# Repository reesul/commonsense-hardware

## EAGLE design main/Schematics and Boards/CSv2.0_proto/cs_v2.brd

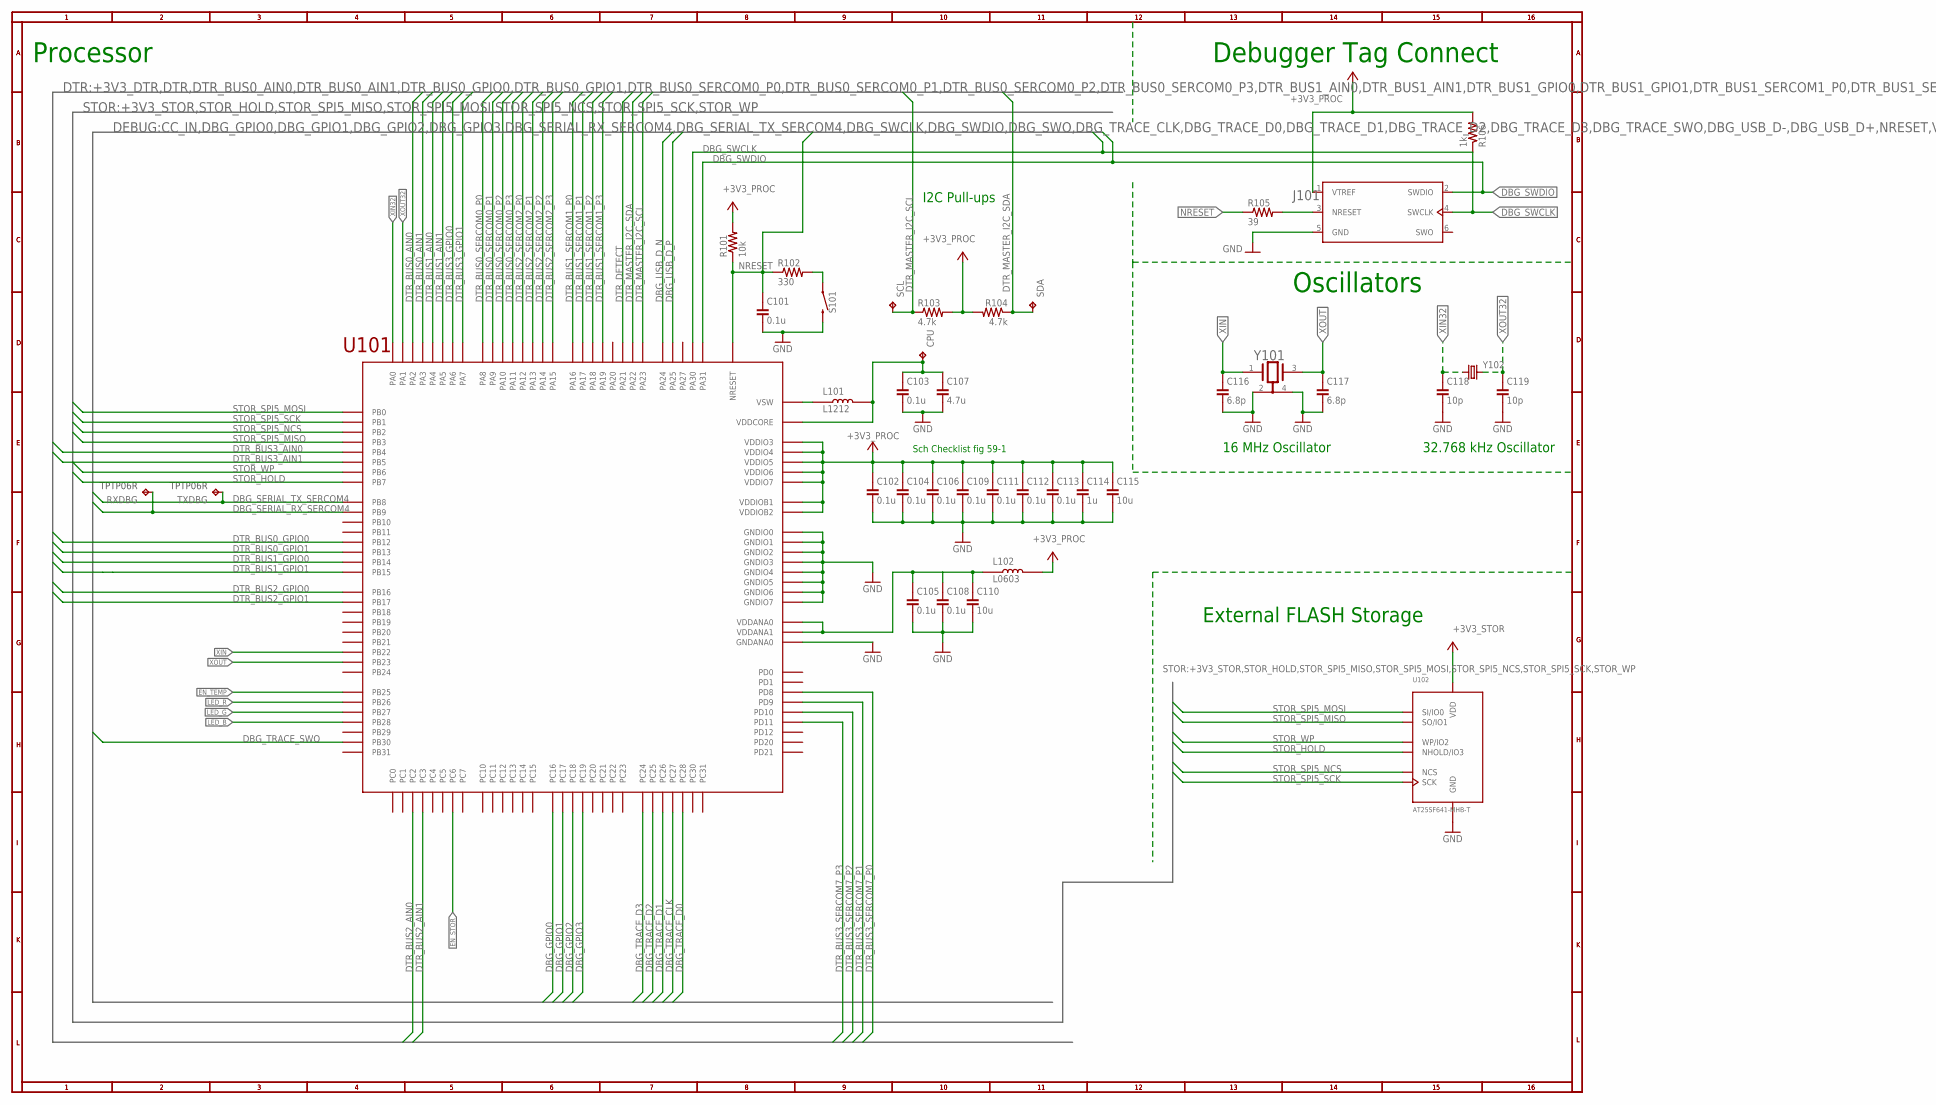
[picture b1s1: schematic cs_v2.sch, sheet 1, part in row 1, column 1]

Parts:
C101, C102, C103, C104, C105, C106, C108, C109, C111, C112, C113: 0.1u; C0402; VOLTAGE 10V; PART_NO C0402C104K8RACTU
C107: 4.7u; C0805; VOLTAGE 10V; PART_NO C0805C475K8RACTU
C110, C115: 10u; C0805; VOLTAGE 10V; PART_NO C0805C106M8RACTU
C114: 1u; C0402; VOLTAGE 10V; PART_NO C0402C105M8PACTU
C116, C117: 6.8p; C0402; PART_NO C0402C689D8GAC7867
C118, C119: 10p; C0402; PART_NO C0402C100C8GACTU
CPU: TPTP06R; TP06R
J101: J-JTAG-CORTEX-NEEDLE6-LEGS; 8.06.16_6-PIN_NEEDLE_ADAPTER_LEGS
L101: L1212; PART_NO LQH3NPN100MMEL
L102: L0603; PART_NO BLM18PG471SN1D
R101: 10k; R0402; PART_NO ERJ-2GEJ103X
R102: 330; R0402; PART_NO ERJ-2GEJ331X
R103, R104: 4.7k; R0402; PART_NO ERJ-2GEJ472X
R105: 39; R0402; PART_NO ERJ-2GEJ390X
R106: 1k; R0402; PART_NO ERJ-2GEJ102X
RXDBG: TPTP06R; TP06R
S101: SW_EVQ-P7L01P_SPST_RA; SW_EVQ-P7L01P
SCL: TPTP06R; TP06R
SDA: TPTP06R; TP06R
TXDBG: TPTP06R; TP06R
U101: ATSAMD51; TFBGA120
U102: AT25SF641-MHB-T; 8-UDFN
Y101: 16M; XTAL_EPSON_TSX3225; PART_NO TSX-3225 16.0000MF09Z-AC3
Y102: ABS07-32.768KHZ-9-T; XTAL320X150X90

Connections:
+3V3_PROC: C102.1, C104.1, C106.1, C109.1, C111.1, C112.1, C113.1, C114.1, C115.1, J101.1 (VTREF), L102.2, R101.2, R103.2, R104.2, R106.2, U101.VDDIO3, U101.VDDIO4, U101.VDDIO5, U101.VDDIO6, U101.VDDIO7, U101.VDDIOB1, U101.VDDIOB2; also elsewhere on the board
+3V3_STOR: U102.8 (VDD); also elsewhere on the board
DBG_GPIO0: U101.PC16; also elsewhere on the board
DBG_GPIO1: U101.PC17; also elsewhere on the board
DBG_GPIO2: U101.PC18; also elsewhere on the board
DBG_GPIO3: U101.PC19; also elsewhere on the board
DBG_SERIAL_RX_SERCOM4: RXDBG.TP, U101.PB09 (PB9); also elsewhere on the board
DBG_SERIAL_TX_SERCOM4: TXDBG.TP, U101.PB08 (PB8); also elsewhere on the board
DBG_SWCLK: J101.4 (SWCLK), R106.1, U101.PA30; also elsewhere on the board
DBG_SWDIO: J101.2 (SWDIO), U101.PA31; also elsewhere on the board
DBG_TRACE_CLK: U101.PC27; also elsewhere on the board
DBG_TRACE_D0: U101.PC28; also elsewhere on the board
DBG_TRACE_D1: U101.PC26; also elsewhere on the board
DBG_TRACE_D2: U101.PC25; also elsewhere on the board
DBG_TRACE_D3: U101.PC24; also elsewhere on the board
DBG_TRACE_SWO: U101.PB30; also elsewhere on the board
DBG_USB_D_N: U101.PA24; also elsewhere on the board
DBG_USB_D_P: U101.PA25; also elsewhere on the board
DTR_BUS0_AIN0: U101.PA02 (PA2); also elsewhere on the board
DTR_BUS0_AIN1: U101.PA03 (PA3); also elsewhere on the board
DTR_BUS0_GPIO0: U101.PB12; also elsewhere on the board
DTR_BUS0_GPIO1: U101.PB13; also elsewhere on the board
DTR_BUS0_SERCOM0_P0: U101.PA08 (PA8); also elsewhere on the board
DTR_BUS0_SERCOM0_P1: U101.PA09 (PA9); also elsewhere on the board
DTR_BUS0_SERCOM0_P2: U101.PA10; also elsewhere on the board
DTR_BUS0_SERCOM0_P3: U101.PA11; also elsewhere on the board
DTR_BUS1_AIN0: U101.PA04 (PA4); also elsewhere on the board
DTR_BUS1_AIN1: U101.PA05 (PA5); also elsewhere on the board
DTR_BUS1_GPIO0: U101.PB14; also elsewhere on the board
DTR_BUS1_GPIO1: U101.PB15; also elsewhere on the board
DTR_BUS1_SERCOM1_P0: U101.PA16; also elsewhere on the board
DTR_BUS1_SERCOM1_P1: U101.PA17; also elsewhere on the board
DTR_BUS1_SERCOM1_P2: U101.PA18; also elsewhere on the board
DTR_BUS1_SERCOM1_P3: U101.PA19; also elsewhere on the board
DTR_BUS2_AIN0: U101.PC02 (PC2); also elsewhere on the board
DTR_BUS2_AIN1: U101.PC03 (PC3); also elsewhere on the board
DTR_BUS2_GPIO0: U101.PB16; also elsewhere on the board
DTR_BUS2_GPIO1: U101.PB17; also elsewhere on the board
DTR_BUS2_SERCOM2_P0: U101.PA12; also elsewhere on the board
DTR_BUS2_SERCOM2_P1: U101.PA13; also elsewhere on the board
DTR_BUS2_SERCOM2_P2: U101.PA14; also elsewhere on the board
DTR_BUS2_SERCOM2_P3: U101.PA15; also elsewhere on the board
DTR_BUS3_AIN0: U101.PB04 (PB4); also elsewhere on the board
DTR_BUS3_AIN1: U101.PB05 (PB5); also elsewhere on the board
DTR_BUS3_GPIO0: U101.PA06 (PA6); also elsewhere on the board
DTR_BUS3_GPIO1: U101.PA07 (PA7); also elsewhere on the board
DTR_BUS3_SERCOM7_P0: U101.PD08 (PD8); also elsewhere on the board
DTR_BUS3_SERCOM7_P1: U101.PD09 (PD9); also elsewhere on the board
DTR_BUS3_SERCOM7_P2: U101.PD10; also elsewhere on the board
DTR_BUS3_SERCOM7_P3: U101.PD11; also elsewhere on the board
DTR_DETECT: U101.PA21; also elsewhere on the board
DTR_MASTER_I2C_SCL: R103.1, SCL.TP, U101.PA23; also elsewhere on the board
DTR_MASTER_I2C_SDA: R104.1, SDA.TP, U101.PA22; also elsewhere on the board
EN_STOR: U101.PC06 (PC6); also elsewhere on the board
EN_TEMP: U101.PB25; also elsewhere on the board
GND: C101.2, C102.2, C103.2, C104.2, C105.2, C106.2, C107.2, C108.2, C109.2, C110.2, C111.2, C112.2, C113.2, C114.2, C115.2, C116.2, C117.2, C118.2, C119.2, J101.5 (GND), S101.2_1 (2), S101.2_2 (2), U101.GNDANA0, U101.GNDIO0, U101.GNDIO1, U101.GNDIO2, U101.GNDIO3, U101.GNDIO4, U101.GNDIO5, U101.GNDIO6, U101.GNDIO7, U102.4 (GND), U102.9 (GND), Y101.2 (1_GND), Y101.4 (2_GND); also elsewhere on the board
JTAG_NRESET: J101.3 (NRESET), R105.2
LED_B: U101.PB28; also elsewhere on the board
LED_G: U101.PB27; also elsewhere on the board
LED_R: U101.PB26; also elsewhere on the board
unnamed: R102.2, S101.1_1 (1), S101.1_2 (1)
NRESET: C101.1, R101.1, R102.1, R105.1, U101.NRESET; also elsewhere on the board
STOR_HOLD: U101.PB07 (PB7), U102.7 (NHOLD/IO3)
STOR_SPI5_MISO: U101.PB03 (PB3), U102.2 (SO/IO1)
STOR_SPI5_MOSI: U101.PB00 (PB0), U102.5 (SI/IO0)
STOR_SPI5_NCS: U101.PB02 (PB2), U102.1 (NCS)
STOR_SPI5_SCK: U101.PB01 (PB1), U102.6 (SCK)
STOR_WP: U101.PB06 (PB6), U102.3 (WP/IO2)
VDDANA: C105.1, C108.1, C110.1, L102.1, U101.VDDANA0, U101.VDDANA1
VDDCORE: C103.1, C107.1, CPU.TP, L101.P$2 (2), U101.VDDCORE
VSW: L101.P$1 (1), U101.VSW
XIN: C116.1, U101.PB22, Y101.1
XIN32: C118.1, U101.PA00 (PA0), Y102.1
XOUT: C117.1, U101.PB23, Y101.3
XOUT32: C119.1, U101.PA01 (PA1), Y102.2

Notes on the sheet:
Sch Checklist fig 59-1
Oscillators
16 MHz Oscillator
32.768 kHz Oscillator
Processor
Debugger Tag Connect
I2C Pull-ups
External FLASH Storage

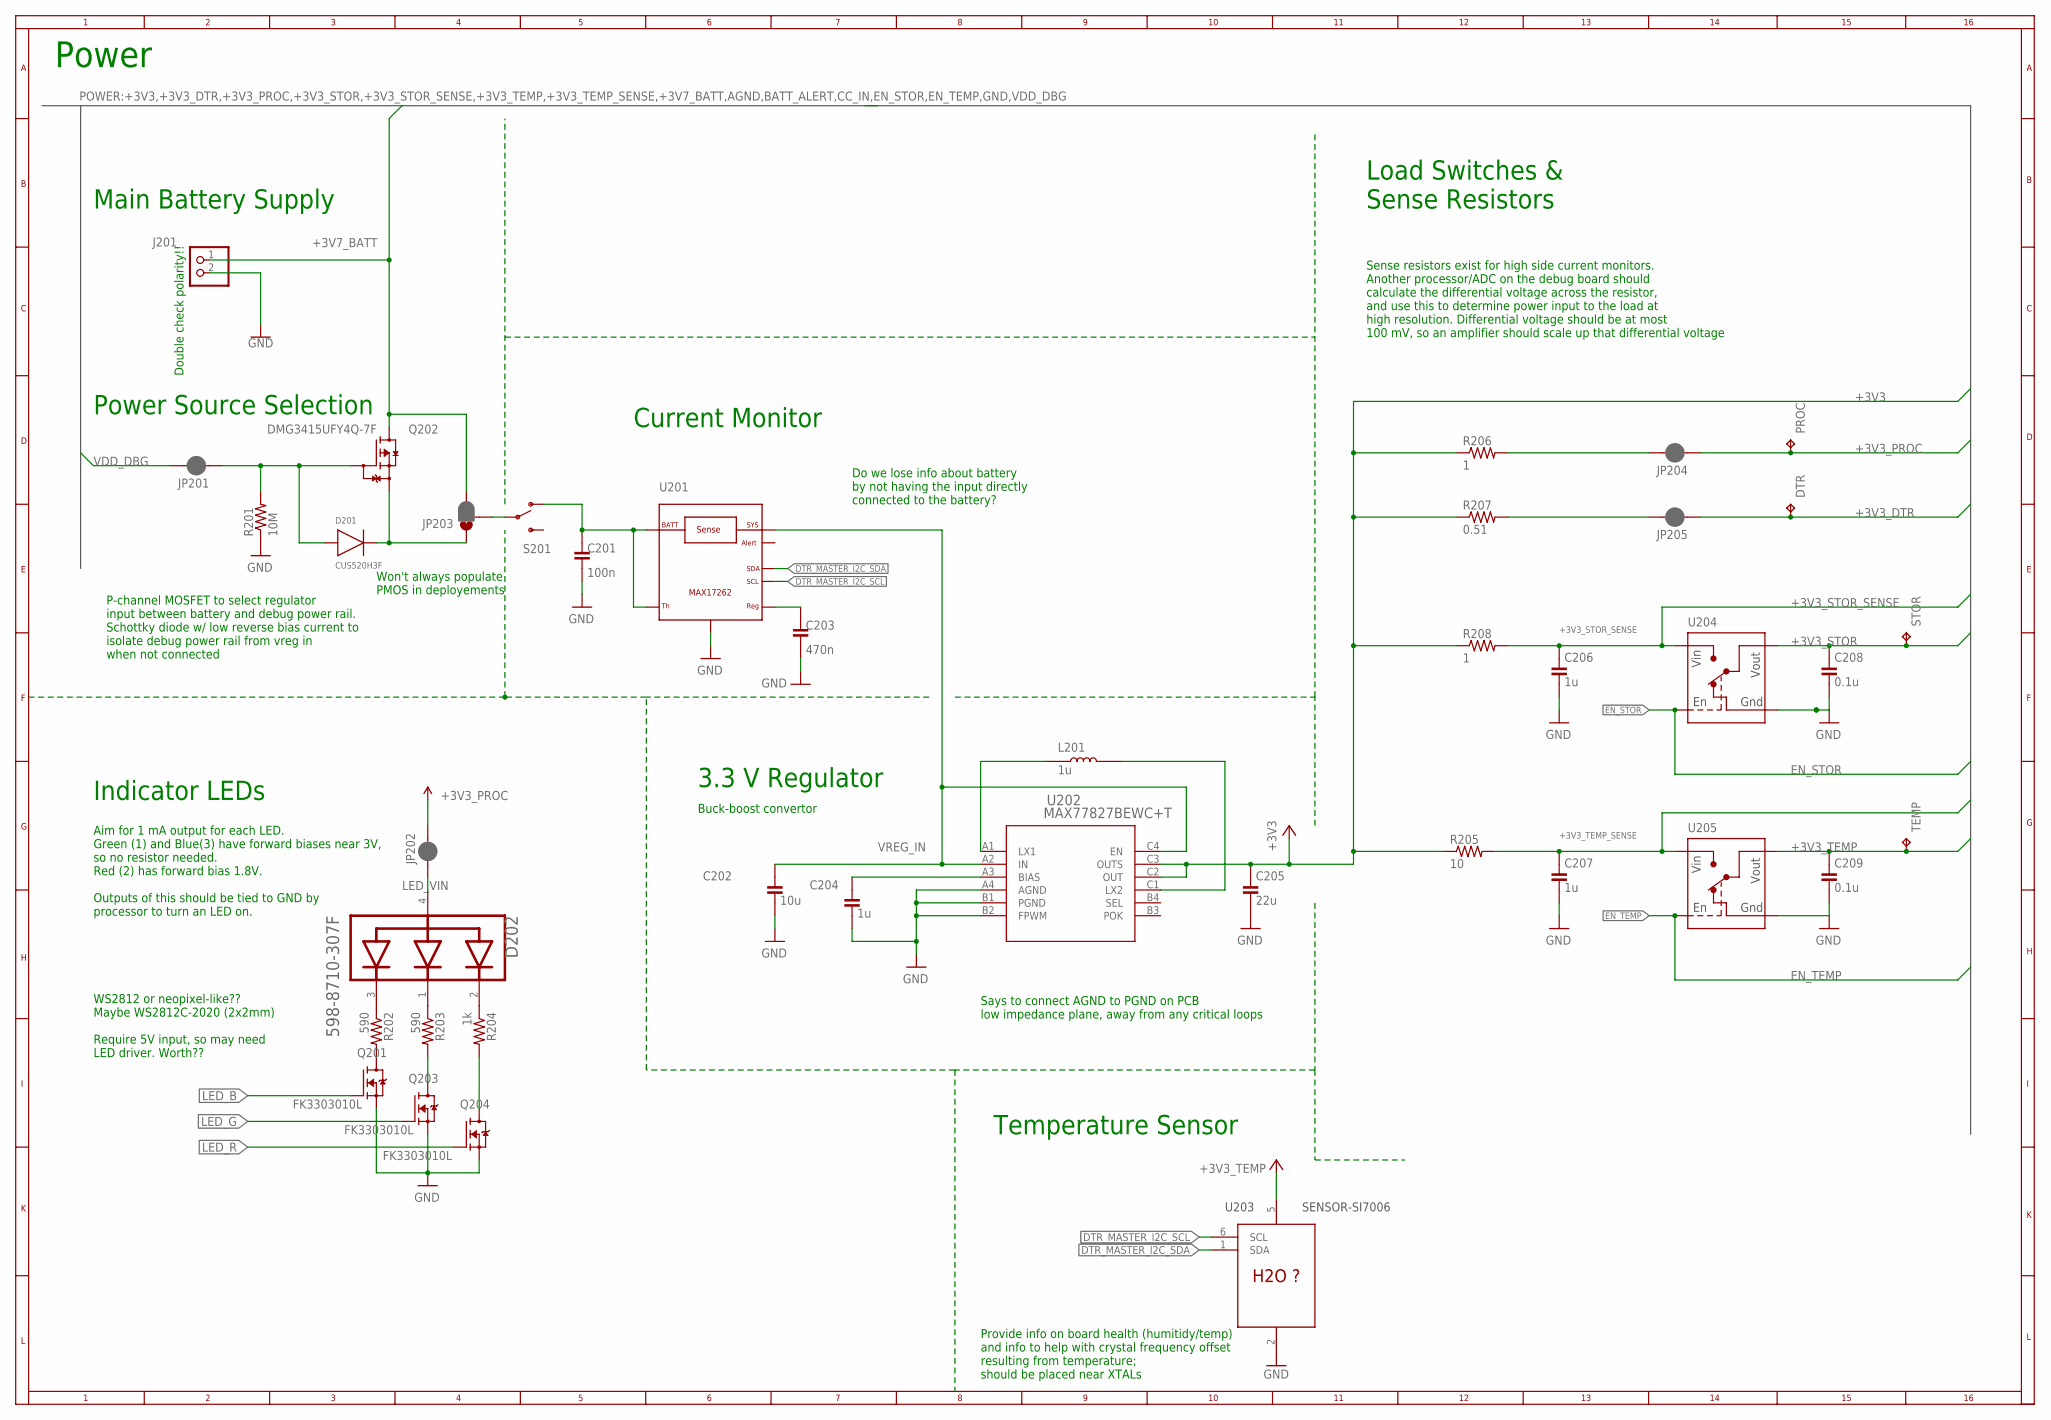
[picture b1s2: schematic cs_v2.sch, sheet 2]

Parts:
C201: 100n; C0402; PART_NO CC0402KRX5R5BB104
C202: 10u; C0603; VOLTAGE 10V; PART_NO C0603C106M8PAC7867
C203: 470n; C0402; PART_NO CC0402KRX5R5BB474
C204: 1u; C0402; VOLTAGE 10V; PART_NO C0402C105K8PACTU
C205: 22u; C0805; VOLTAGE 10V; PART_NO C0805C226M8PAC7800
C206, C207: 1u; C0402; VOLTAGE 10V; PART_NO C0402C105M8PACTU
C208, C209: 0.1u; C0402; VOLTAGE 10V; PART_NO C0402C104K8RACTU
D201: CUS520H3F
D202: DIALIGHT_RGBLED_598-8710-307FDIALIGHT_598-8710-30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; DIALIGHT_0606_598-8710-307F_0; PART_NO 598-8710-307F
DTR: TPTP06R; TP06R
J201: J-JST2-SMT-RA; JST-PH-2-SMT-RA; PART_NO S2B-PH-SM4-TB(LF)(SN)
JP201, JP202, JP204, JP205: JUMPER-SMT_2_NC_PASTE_NO-SILK; SMT-JUMPER_2_NC_PASTE_NO-SILK
JP203: JUMPER-SMT_3_1-NC_PASTE_NO-SILK; SMT-JUMPER_3_1-NC_PASTE_NO-SILK
L201: 1u; L1008; PART_NO CIGT252010EH1R0MNE
PROC: TPTP06R; TP06R
Q201, Q203, Q204: FK3303010L; SSSMINI3
Q202: DMG3415UFY4Q-7F; X2-DFN2015-3; PART_NO DMG3415UFY4Q-7
R201: 10M; R0402; PART_NO ERJ-2GEJ106X
R202, R203: 590; R0402; PART_NO ERJ-2RKF5900X
R204: 1k; R0402; PART_NO ERA-2AED102X
R205: 10; R0603; PART_NO ERA-3AHD100V
R206, R208: 1; R0603; PART_NO ERJ-3RQF1R0V
R207: 0.51; R0603; PART_NO ERJ-3BQFR51V
S201: SLIDESWITCH-SPDT-SMD-RIGHT-ANGLE; SWITCH_SPST_SMD_A; PART_NO CUS-12TB
STOR: TPTP06R; TP06R
TEMP: TPTP06R; TP06R
U201: COULOMB-MAX17262; BGA9N40P3X3_144X146X69N; PART_NO MAX17262REWL+T
U202: MAX77827BEWC+T; 12-WLP; PART_NO MAX77827BEWC+T
U203: SENSOR-SI7006; DFN-06; PART_NO SI7021-A20-GM1R
U204, U205: LOADSWITCH-MIC94164; WLCSP6_2X3; PART_NO MIC94164YCS-TR

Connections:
+3V3: C205.1, R205.1, R206.1, R207.1, R208.1, U202.C2 (OUT), U202.C3 (OUTS); also elsewhere on the board
+3V3_DTR: DTR.TP, JP205.1; also elsewhere on the board
+3V3_DTR_SENSE: JP205.2, R207.2
+3V3_PROC: JP202.2, JP204.1, PROC.TP; also elsewhere on the board
+3V3_PROC_SENSE: JP204.2, R206.2
+3V3_STOR: C208.1, STOR.TP, U204.A1 (VOUT), U204.B1 (VOUT); also elsewhere on the board
+3V3_STOR_SENSE: C206.1, R208.2, U204.A2 (VIN), U204.B2 (VIN); also elsewhere on the board
+3V3_TEMP: C209.1, TEMP.TP, U203.5 (V), U205.A1 (VOUT), U205.B1 (VOUT)
+3V3_TEMP_SENSE: C207.1, R205.2, U205.A2 (VIN), U205.B2 (VIN); also elsewhere on the board
+3V7_BATT: J201.1 (2), JP203.3, Q202.3-1 (D), Q202.3-2 (D); also elsewhere on the board
CC_IN: C201.1, S201.1 (O), U201.A1 (TH), U201.A2 (BATT)
DTR_MASTER_I2C_SCL: U201.B1 (SCL), U203.6 (SCL); also elsewhere on the board
DTR_MASTER_I2C_SDA: U201.C1 (SDA), U203.1 (SDA); also elsewhere on the board
EN_STOR: U204.C2 (ENABLE); also elsewhere on the board
EN_TEMP: U205.C2 (ENABLE); also elsewhere on the board
GND: C201.2, C202.2, C203.2, C204.2, C205.2, C206.2, C207.2, C208.2, C209.2, J201.2 (1), Q201.1 (S), Q203.1 (S), Q204.1 (S), R201.1, U201.C3 (GND), U202.A4 (AGND), U202.B1 (PGND), U202.B2 (FPWM), U203.2 (GND), U204.C1 (GND), U205.C1 (GND); also elsewhere on the board
LED_B: Q201.3 (G); also elsewhere on the board
LED_G: Q203.3 (G); also elsewhere on the board
LED_R: Q204.3 (G); also elsewhere on the board
LED_VIN: D202.4 (COMMON_ANODE), JP202.1
unnamed: D202.3 (BLUE_CATHODE), R202.1
unnamed: D202.1 (GREEN_CATHODE), R203.1
unnamed: C203.1, U201.C2 (REG)
unnamed: D202.2 (RED_CATHODE), R204.1
unnamed: Q201.2 (D), R202.2
unnamed: Q203.2 (D), R203.2
unnamed: Q204.2 (D), R204.2
VDD_DBG: JP201.2; also elsewhere on the board
VDD_DBG_JMP: D201.P, JP201.1, Q202.1 (G), R201.2
VDD_SW: D201.N, JP203.1, Q202.2 (S)
VDD_SW_IN: JP203.2, S201.2
VREG_BIAS: C204.1, U202.A3 (BIAS)
VREG_IN: C202.1, U201.B3 (SYS), U202.A2 (IN), U202.C4 (EN)
VREG_LX1: L201.1, U202.A1 (LX1)
VREG_LX2: L201.2, U202.C1 (LX2)

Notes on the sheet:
Double check polarity!!
Sense resistors exist for high side current monitors. Another processor/ADC on the debug board should calculate the differential voltage across the resistor, and use this to determine power input to the load at high resolution. Differential voltage should be at most 100 mV, so an amplifier should s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
Power
P-channel MOSFET to select regulator input between battery and debug power rail. Schottky diode w/ low reverse bias current to isolate debug power rail from vreg in when not connected
3.3 V Regulator
Power Source Selection
Main Battery Supply
Load Switches & Sense Resistors
Buck-boost convertor
Aim for 1 mA output for each LED. Green (1) and Blue(3) have forward biases near 3V, so no resistor needed. Red (2) has forward bias 1.8V. Outputs of this should be tied to GND by processor to turn an LED on.
Indicator LEDs
WS2812 or neopixel-like?? Maybe WS2812C-2020 (2x2mm) Require 5V input, so may need LED driver. Worth??
Temperature Sensor
Says to connect AGND to PGND on PCB low impedance plane, away from any critical loops
Provide info on board health (humitidy/temp) and info to help with crystal frequency offset resulting from temperature; should be placed near XTALs
Current Monitor
Do we lose info about battery by not having the input directly connected to the battery?
Won't always populate PMOS in deployements

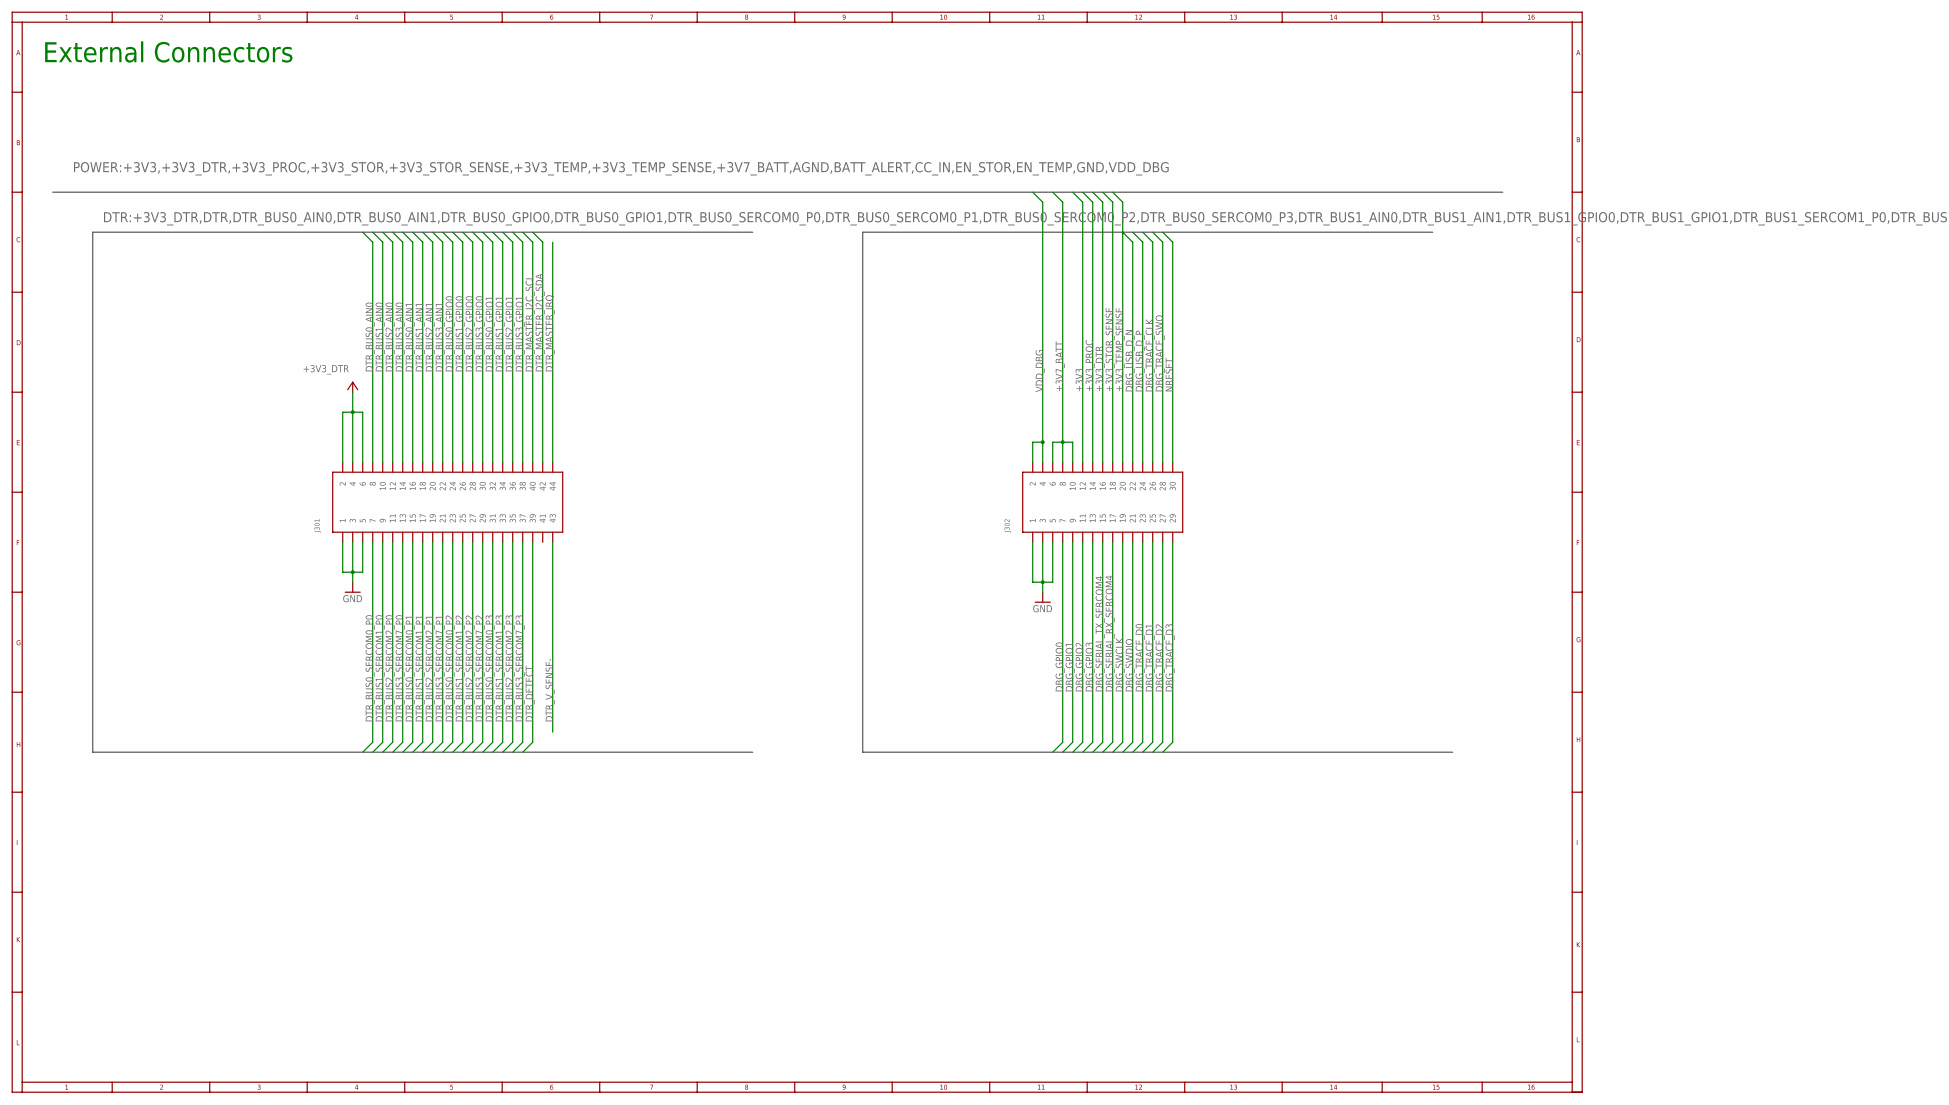
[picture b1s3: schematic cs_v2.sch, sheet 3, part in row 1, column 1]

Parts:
J301: HIROSE-DF40_44-PIN_CONNECTORS-RECEPTACLE; HRS_DF40HC(3.0)-44DS-0.4V(51); PART_NO DF40HC(3.0)-44DS-0.4V(51)
J302: HIROSE-DF40_30-PIN_CONNECTORS-RECEPTACLE; HRS_DF40HC(3.0)-30DS-0.4V(51); PART_NO DF40HC(3.0)-30DS-0.4V(58)

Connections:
+3V3: J302.12; also elsewhere on the board
+3V3_DTR: J301.2, J301.4, J301.6, J302.16; also elsewhere on the board
+3V3_PROC: J302.14; also elsewhere on the board
+3V3_STOR_SENSE: J302.18; also elsewhere on the board
+3V3_TEMP_SENSE: J302.20; also elsewhere on the board
+3V7_BATT: J302.6, J302.8, J302.10; also elsewhere on the board
DBG_GPIO0: J302.7; also elsewhere on the board
DBG_GPIO1: J302.9; also elsewhere on the board
DBG_GPIO2: J302.11; also elsewhere on the board
DBG_GPIO3: J302.13; also elsewhere on the board
DBG_SERIAL_RX_SERCOM4: J302.17; also elsewhere on the board
DBG_SERIAL_TX_SERCOM4: J302.15; also elsewhere on the board
DBG_SWCLK: J302.19; also elsewhere on the board
DBG_SWDIO: J302.21; also elsewhere on the board
DBG_TRACE_CLK: J302.26; also elsewhere on the board
DBG_TRACE_D0: J302.23; also elsewhere on the board
DBG_TRACE_D1: J302.25; also elsewhere on the board
DBG_TRACE_D2: J302.27; also elsewhere on the board
DBG_TRACE_D3: J302.29; also elsewhere on the board
DBG_TRACE_SWO: J302.28; also elsewhere on the board
DBG_USB_D_N: J302.22; also elsewhere on the board
DBG_USB_D_P: J302.24; also elsewhere on the board
DTR_BUS0_AIN0: J301.8; also elsewhere on the board
DTR_BUS0_AIN1: J301.16; also elsewhere on the board
DTR_BUS0_GPIO0: J301.24; also elsewhere on the board
DTR_BUS0_GPIO1: J301.32; also elsewhere on the board
DTR_BUS0_SERCOM0_P0: J301.7; also elsewhere on the board
DTR_BUS0_SERCOM0_P1: J301.15; also elsewhere on the board
DTR_BUS0_SERCOM0_P2: J301.23; also elsewhere on the board
DTR_BUS0_SERCOM0_P3: J301.31; also elsewhere on the board
DTR_BUS1_AIN0: J301.10; also elsewhere on the board
DTR_BUS1_AIN1: J301.18; also elsewhere on the board
DTR_BUS1_GPIO0: J301.26; also elsewhere on the board
DTR_BUS1_GPIO1: J301.34; also elsewhere on the board
DTR_BUS1_SERCOM1_P0: J301.9; also elsewhere on the board
DTR_BUS1_SERCOM1_P1: J301.17; also elsewhere on the board
DTR_BUS1_SERCOM1_P2: J301.25; also elsewhere on the board
DTR_BUS1_SERCOM1_P3: J301.33; also elsewhere on the board
DTR_BUS2_AIN0: J301.12; also elsewhere on the board
DTR_BUS2_AIN1: J301.20; also elsewhere on the board
DTR_BUS2_GPIO0: J301.28; also elsewhere on the board
DTR_BUS2_GPIO1: J301.36; also elsewhere on the board
DTR_BUS2_SERCOM2_P0: J301.11; also elsewhere on the board
DTR_BUS2_SERCOM2_P1: J301.19; also elsewhere on the board
DTR_BUS2_SERCOM2_P2: J301.27; also elsewhere on the board
DTR_BUS2_SERCOM2_P3: J301.35; also elsewhere on the board
DTR_BUS3_AIN0: J301.14; also elsewhere on the board
DTR_BUS3_AIN1: J301.22; also elsewhere on the board
DTR_BUS3_GPIO0: J301.30; also elsewhere on the board
DTR_BUS3_GPIO1: J301.38; also elsewhere on the board
DTR_BUS3_SERCOM7_P0: J301.13; also elsewhere on the board
DTR_BUS3_SERCOM7_P1: J301.21; also elsewhere on the board
DTR_BUS3_SERCOM7_P2: J301.29; also elsewhere on the board
DTR_BUS3_SERCOM7_P3: J301.37; also elsewhere on the board
DTR_DETECT: J301.39; also elsewhere on the board
DTR_MASTER_I2C_SCL: J301.40; also elsewhere on the board
DTR_MASTER_I2C_SDA: J301.42; also elsewhere on the board
DTR_MASTER_IRQ: J301.44
DTR_V_SENSE-: J301.43
GND: J301.1, J301.3, J301.5, J302.1, J302.3, J302.5; also elsewhere on the board
NRESET: J302.30; also elsewhere on the board
VDD_DBG: J302.2, J302.4; also elsewhere on the board

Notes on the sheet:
External Connectors

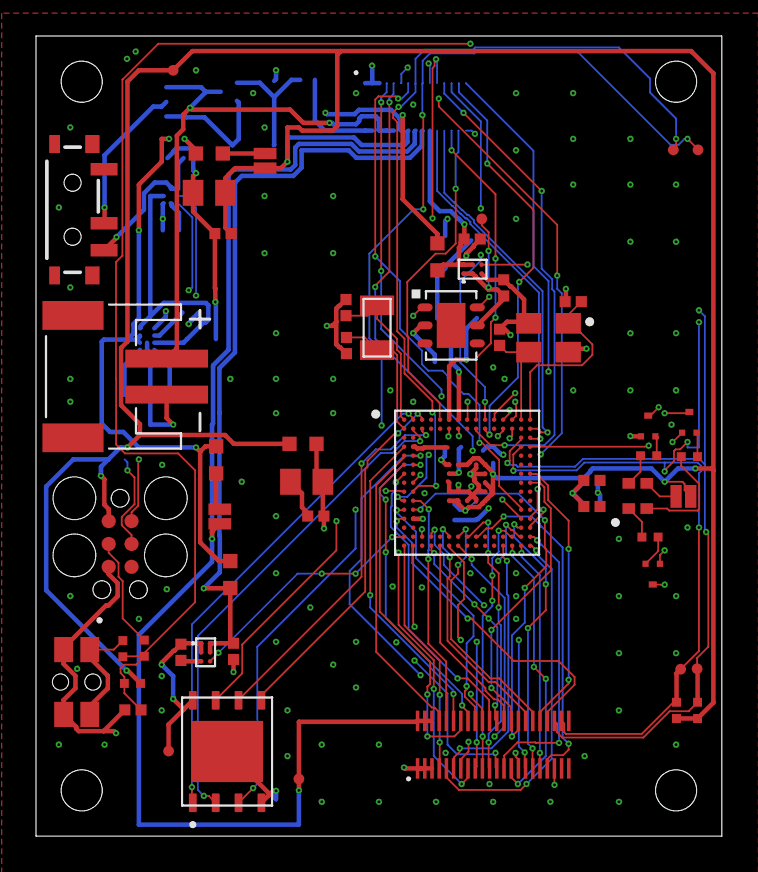
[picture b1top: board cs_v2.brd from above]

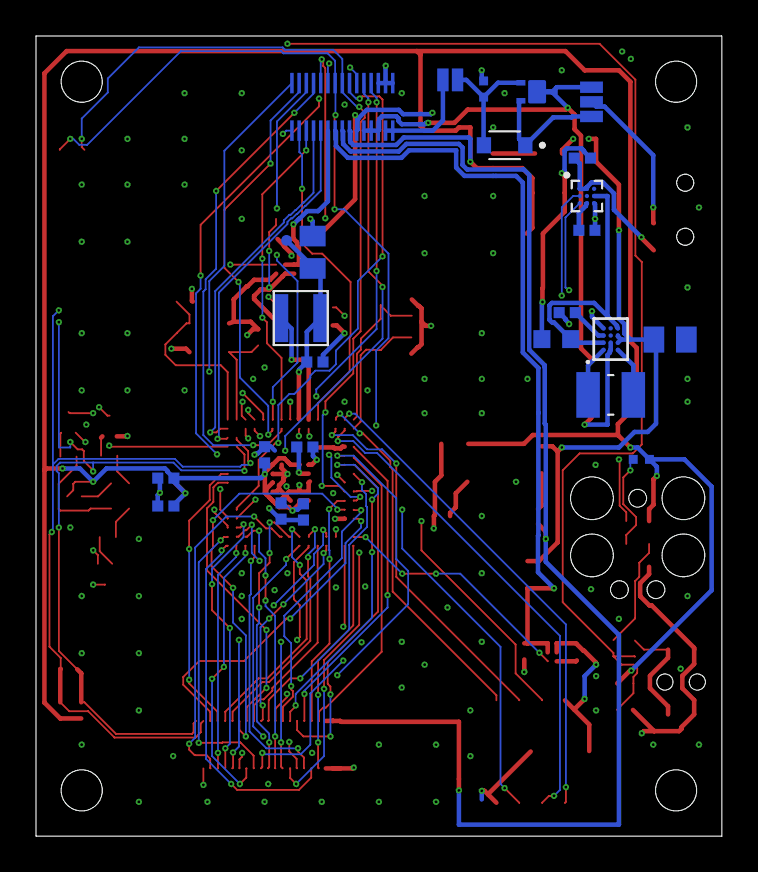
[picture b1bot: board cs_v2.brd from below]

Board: 4 copper layers, 38.1 x 44.5 mm, 80 parts (25 on the bottom side), 100 nets.

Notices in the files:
parts and their libraries:
Graphics: Copyright (c) 2004-2019 Bob Iannucci
Graphics: All rights reserved worldwide.
Oscillators: COPYRIGHT: Copyright (C) 2018 Accelerated Designs. All rights reserved
Inductors: COPYRIGHT: Copyright (C) 2016 Accelerated Designs. All rights reserved
